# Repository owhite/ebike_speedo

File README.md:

# EBIKE SPEEDOMETER FEATURES
* Completely uninteresting 14 segment LED displays
* Serial data --> board --> BLE to smartphone
* Compatible with [MESC controller](https://github.com/davidmolony/MESC_Firmware)

## Operation
Device connects to an ESC (e.g. the [MP2](https://github.com/badgineer/CCC_ESC) with a [F405 pill](https://github.com/davidmolony/F405_pill)) and receives json data via a serial output. Typcial data stream could include:
```
{"amps": 10, "volts": 20, "rpm": 200, "temp": 90}
```
But you can configure the F405 to send other values, but the speedometer is expecting the above tags and ignores others. The speedometer uses these values as ints that will be displayed on the 14 segment LED. RPM will be converted to MPH prior to display. 

Regardless of the values or data structure received, the entired data stream is passed on to a bluetooth device which can be captured on your smartphone using an app like [Serial Bluetooth Terminal](https://play.google.com/store/apps/details?id=de.kai_morich.serial_bluetooth_terminal). 

## Programming
* Use the [STM32CubeIDE](https://www.st.com/en/development-tools/stm32cubeide.html) to progam the microcontroller on the ESC
* Use [platformio](https://platformio.org/) for the ESP32. 

## ESP32 quirks
There are conflicts between bootstrapping capability and usage of some pins. If you notice your board wont program unless you keep the button depressed, it might be due to this conflict.

This reqiures that you burn the flash voltage selection eFuses change the internal regulator’s output voltage to 3.3 V. This was fixed with using a tool from [espressif](https://docs.espressif.com/projects/esptool/en/latest/esp32s3/espefuse/index.html): 

```
$ espefuse.py set_flash_voltage 3.3V --port /dev/cu.usbserial-01562A86
```
be sure to use the appropriate port name. 

## Speedometer operation
* Assemble PCB
* Set the following parameters in ESP32 code:
```
#define POLEPAIRS    5
#define CIRCUMFERENCE 78.5 // circumference in cm of wheel
#define MAXTEMP 65 
// for the range when it provides a percentage
#define MINVOLTAGE 86.4    // lower bound of voltage
#define MAXVOLTAGE 104.0   // 24s lipos fully charge

```
* Upload code to ESP32 using platformio
* Press top button to change LED display
* Display shows: "M", "A", "V" "T" for MPH, amps, battery voltage, and temperature
* Find "ESP32 Speedometer" on your smartphone
* Gather data using an app like [Serial Bluetooth Terminal](https://play.google.com/store/apps/details?id=de.kai_morich.serial_bluetooth_terminal)
* Note on the json data there's a mS value, press lower button to reset to zero

## BOM
* Adafruit Quad Alphanumeric Display w/ backpack
* Adafruit HUZZAH32 – ESP32 Feather Board
* PCB (gerbers are [here](V1.1/gerbers))
* Two 10k 0805 resistors
* [TS14-1212-70-BK-160-SCR-D](https://www.cuidevices.com/product/resource/ts14.pdf) tactile switches
* 0.1 inch spacing header boards
* This [housing](3D_model/speedo_housing.stl) might be useful

Let's play: how tall is your stack of boards!?

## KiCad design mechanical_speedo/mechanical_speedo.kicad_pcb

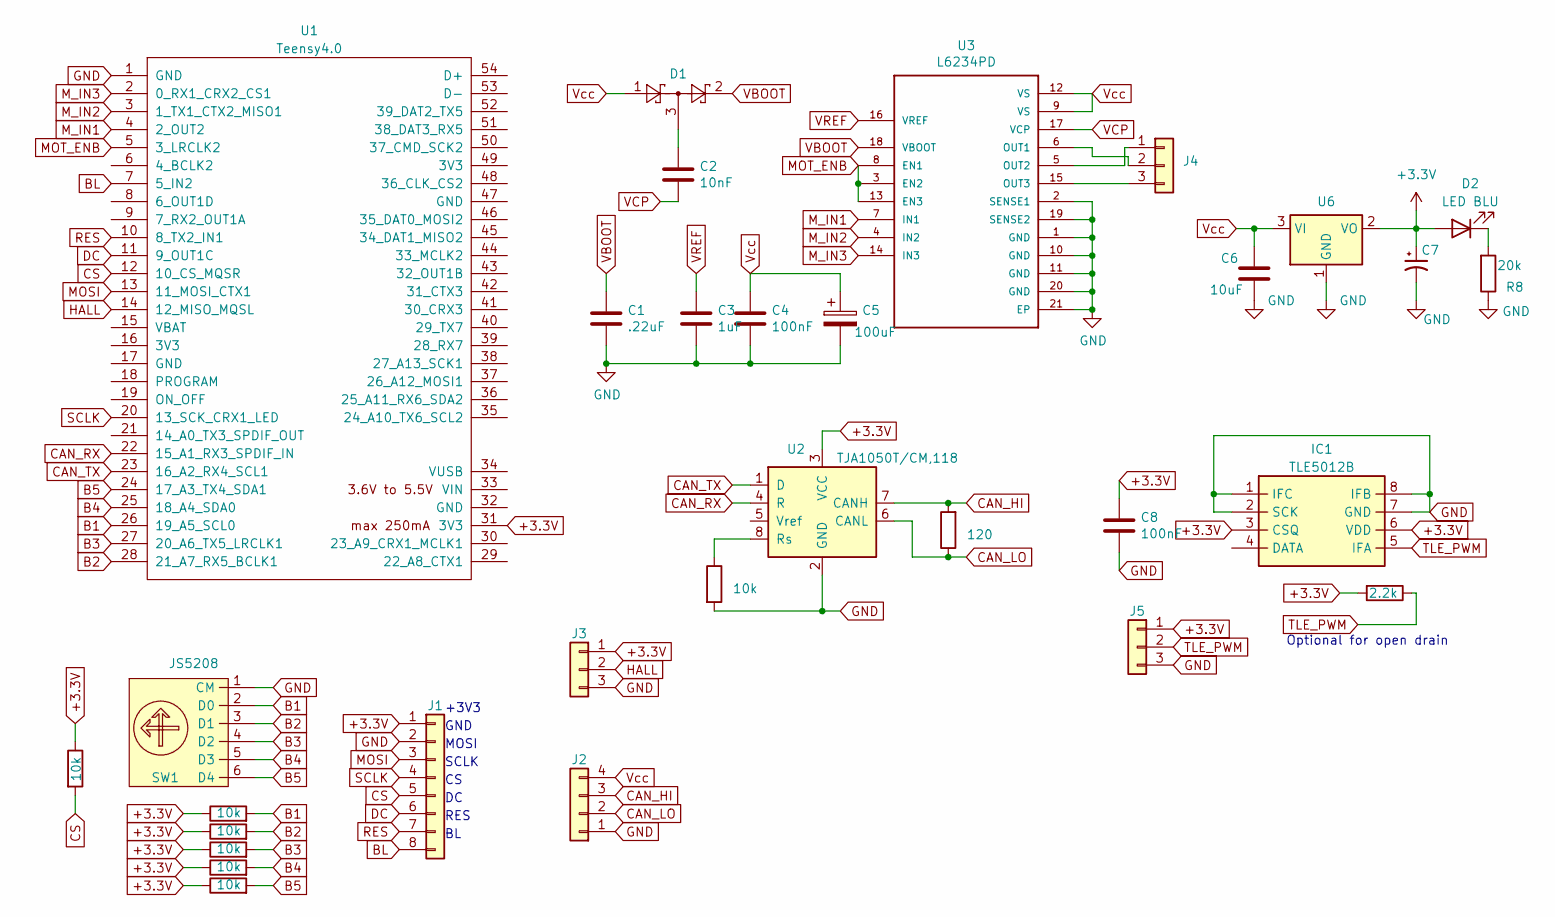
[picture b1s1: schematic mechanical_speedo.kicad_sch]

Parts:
C1: .22uF; C_0805_2012Metric; LCSC C5378
C2: 10nF; C_0603_1608Metric; LCSC C57112
C3: 1uF; C_0805_2012Metric; LCSC C28323
C4, C8: 100nF; C_0603_1608Metric; LCSC C14663
C5: 100uF; CP_EIA-3528-21_Kemet-B; LCSC C16133
C6: 10uF; C_0805_2012Metric; LCSC C15850
C7: C_Polarized_Small_US; CP_EIA-3216-18_Kemet-A; LCSC C7171
D1: BAT54S; SOT-23; LCSC C19726
D2: LED BLU; LED_0603_1608Metric; LCSC C72041
IC1: TLE5012B; SOIC127P600X175-8N; Mouser Part Number 726-TLE5012BE5000X
J1: Conn_01x08; 8_hole
J2: Conn_01x04; my_4_tab_edge
J3, J4, J5: Conn_01x03; PinHeader_1x03_P2.54mm_Vertical
R1, R2, R3, R4, R5, R6, R9: 10k; R_0805_2012Metric; LCSC C25804
R7: 120; R_0805_2012Metric; LCSC C17437
R8: 20k; R_0603_1608Metric; LCSC C4184
R11: 2.2k; R_0603_1608Metric; LCSC C4184
SW1: JS5208; SW_JS5208; LCSC C3029619
U1: Teensy4.0; Teensy32
U2: TJA1050T/CM,118; SOIC-8_3.9x4.9mm_P1.27mm; LCSC C6952
U3: L6234PD
U6: LD1117S18TR_SOT223; SOT-223-3_TabPin2; LCSC C2984862

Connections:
+3.3V: C7.1, C8.1, D2.2 (A), IC1.3 (CSQ), IC1.6 (VDD), J1.1, J3.1, J5.1, R1.1, R2.1, R4.1, R5.1, R6.1, R9.1, R11.2, U1.31 (3V3), U2.3 (VCC), U6.2 (VO)
B1: R6.2, SW1.2 (D0), U1.26 (19_A5_SCL0)
B2: R5.2, SW1.3 (D1), U1.28 (21_A7_RX5_BCLK1)
B3: R4.2, SW1.4 (D2), U1.27 (20_A6_TX5_LRCLK1)
B4: R2.2, SW1.5 (D3), U1.25 (18_A4_SDA0)
B5: R1.2, SW1.6 (D4), U1.24 (17_A3_TX4_SDA1)
BL: J1.8, U1.7 (5_IN2)
CAN_HI: J2.3, R7.2, U2.7 (CANH)
CAN_LO: J2.2, R7.1, U2.6 (CANL)
CAN_RX: U1.22 (15_A1_RX3_SPDIF_IN), U2.4 (R)
CAN_TX: U1.23 (16_A2_RX4_SCL1), U2.1 (D)
CS: J1.5, R9.2, U1.12 (10_CS_MQSR)
DC: J1.6, U1.11 (9_OUT1C)
GND: C1.2, C3.2, C4.2, C5.2, C6.2, C7.2, C8.2, IC1.1 (IFC), IC1.2 (SCK), IC1.7 (GND), IC1.8 (IFB), J1.2, J2.1, J3.3, J5.3, R3.2, R8.1, SW1.1 (CM), U1.1 (GND), U2.2 (GND), U3.1 (GND), U3.2 (SENSE1), U3.10 (GND), U3.11 (GND), U3.19 (SENSE2), U3.20 (GND), U3.21 (EP), U6.1 (GND)
HALL: J3.2, U1.14 (12_MISO_MQSL)
MOSI: J1.3, U1.13 (11_MOSI_CTX1)
MOT_ENB: U1.5 (3_LRCLK2), U3.3 (EN2), U3.8 (EN1), U3.13 (EN3)
M_IN1: U1.4 (2_OUT2), U3.7 (IN1)
M_IN2: U1.3 (1_TX1_CTX2_MISO1), U3.4 (IN2)
M_IN3: U1.2 (0_RX1_CRX2_CS1), U3.14 (IN3)
unnamed: C2.1, D1.3
unnamed: D2.1 (K), R8.2
unnamed: J4.1, U3.5 (OUT2)
unnamed: J4.2, U3.6 (OUT1)
unnamed: J4.3, U3.15 (OUT3)
unnamed: R3.1, U2.8 (Rs)
RES: J1.7, U1.10 (8_TX2_IN1)
SCLK: J1.4, U1.20 (13_SCK_CRX1_LED)
TLE_PWM: IC1.5 (IFA), J5.2, R11.1
VBOOT: C1.1, D1.2, U3.18 (VBOOT)
VCP: C2.2, U3.17 (VCP)
VREF: C3.1, U3.16 (VREF)
Vcc: C4.1, C5.1, C6.1, D1.1, J2.4, U3.9 (VS), U3.12 (VS), U6.3 (VI)

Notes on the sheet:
MOSI
Optional for open drain
RES
GND
+3V3
SCLK

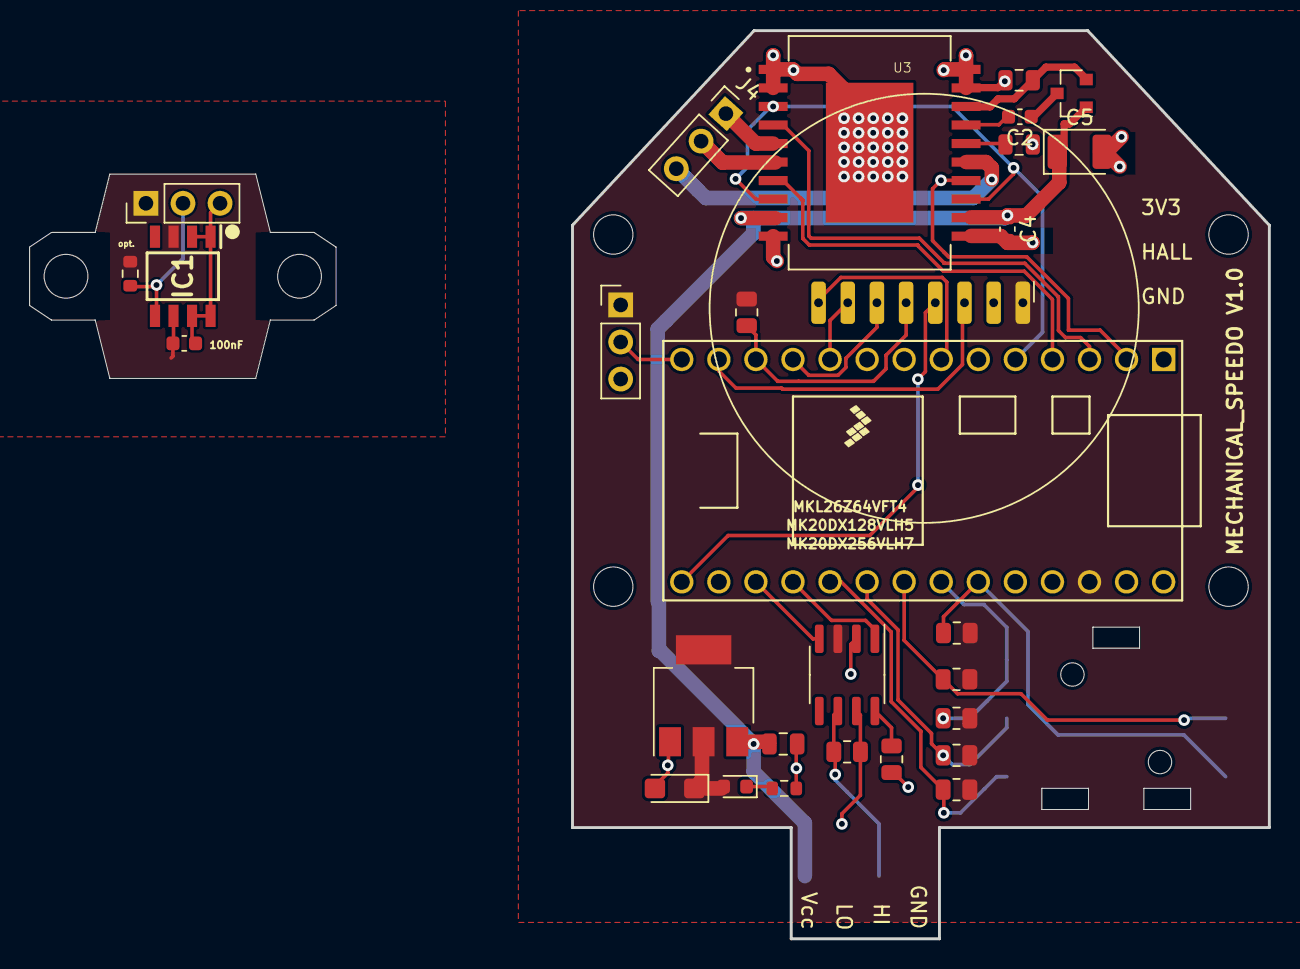
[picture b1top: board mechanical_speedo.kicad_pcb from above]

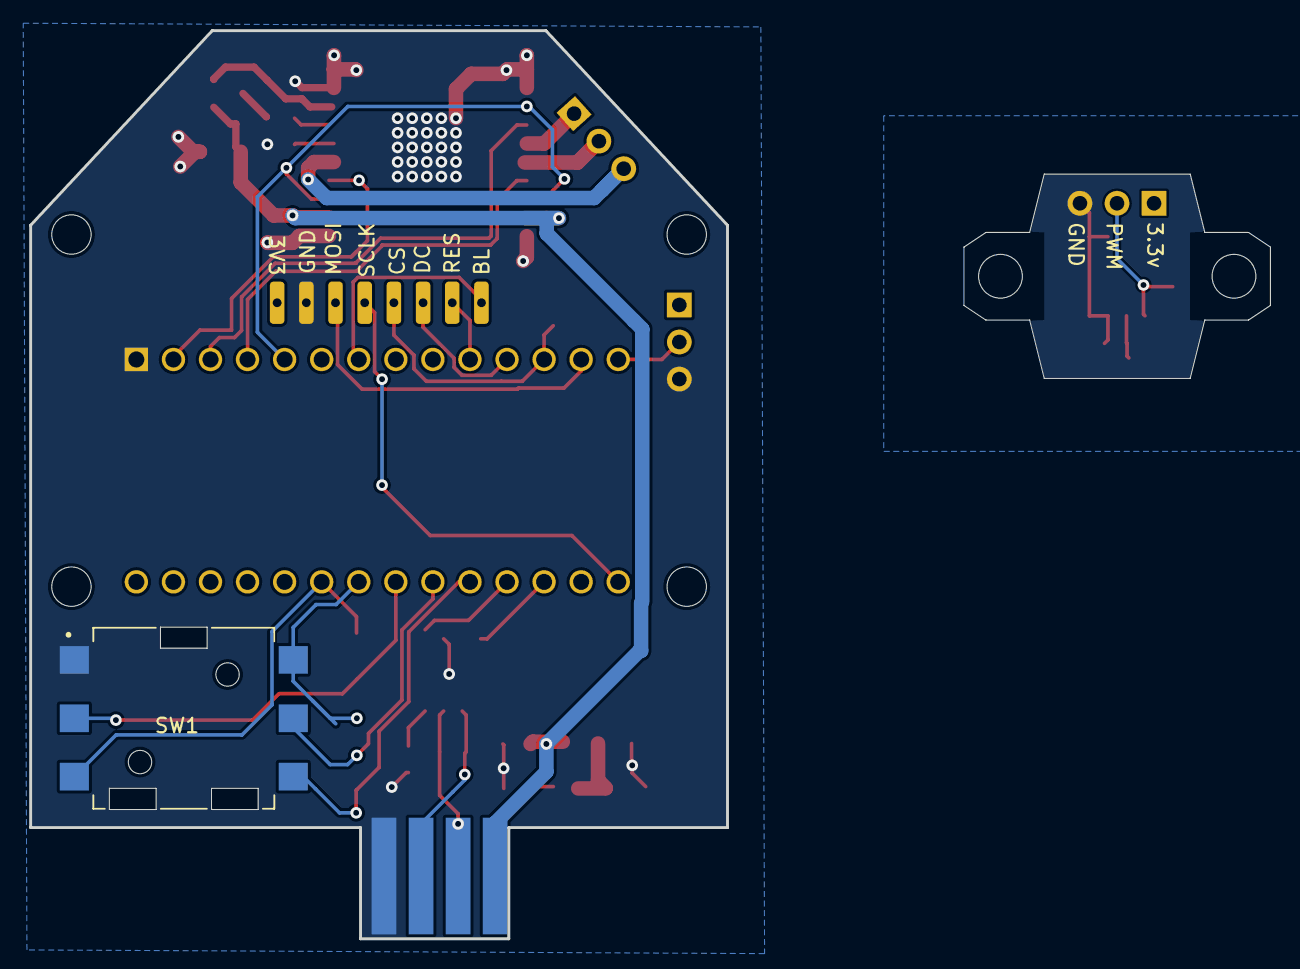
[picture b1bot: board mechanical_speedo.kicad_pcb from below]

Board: 2 copper layers, 84.9 x 62.2 mm, 31 parts (2 on the bottom side), 33 nets.

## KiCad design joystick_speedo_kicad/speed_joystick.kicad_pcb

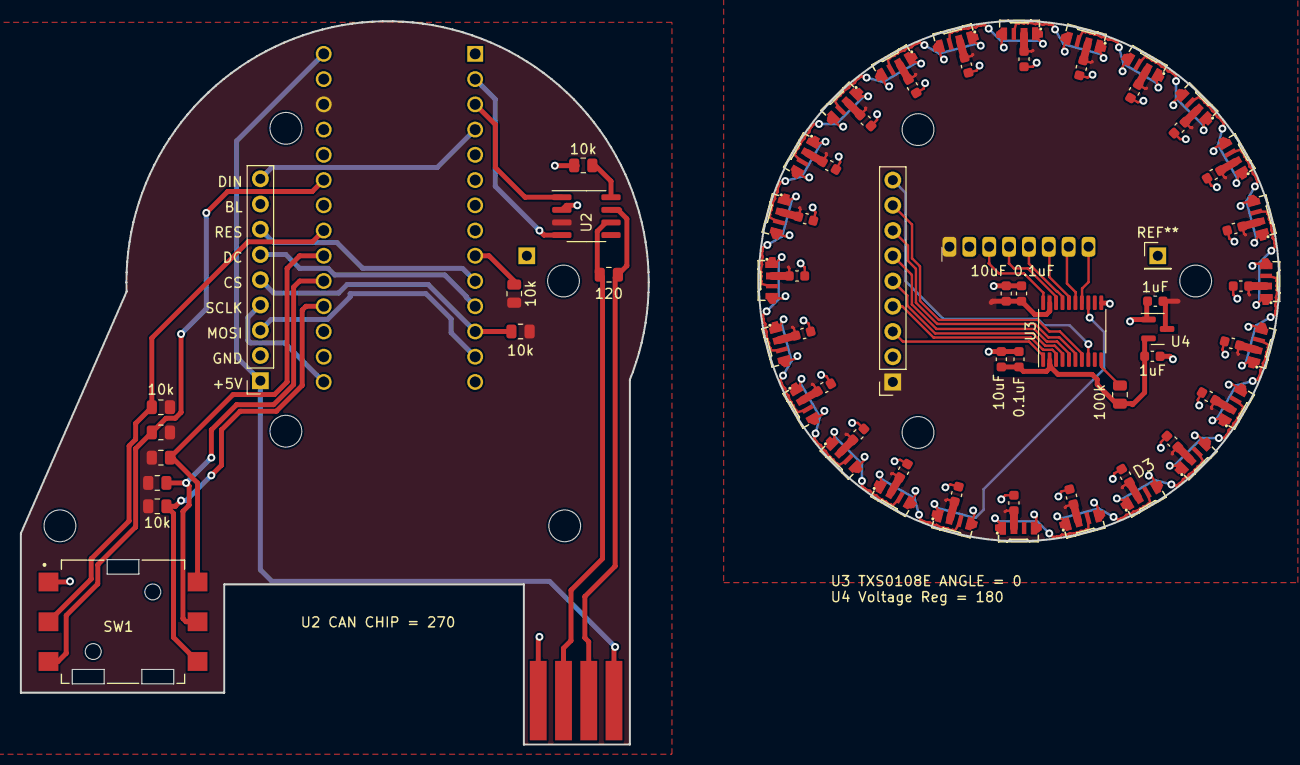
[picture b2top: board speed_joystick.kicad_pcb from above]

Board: 2 copper layers, 126.6 x 72.8 mm, 73 parts (1 on the bottom side), 62 nets.

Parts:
C1, C2, C3, C4, C5, C6, C7, C8, C9, C10, C11, C12, C13, C14, C15, C16, C17, C18, C19, C20, C21, C22, C23, C24, C25, C26: 0.1uF; C_0603_1608Metric
C27, C28: 1uF; C_0603_1608Metric
C29, C30: 10uF; C_0603_1608Metric
D1, D2, D3, D4, D5, D6, D7, D8, D9, D10, D11, D12, D13, D14, D15, D16, D17, D18, D19, D20, D21, D22, D23, D24: SK6812; LED-SMD_4P-L4.0-W1.6-L
J1: Conn_01x08; 8_hole
J2: Conn_01x04; my_4_tab_edge
J3, J4: Conn_01x09; PinSocket_1x09_P2.54mm_Vertical
R1, R2, R3, R4, R5, R6, R9, R10: 10k; R_0805_2012Metric
R7: 120; R_0805_2012Metric
R8: 100k; R_0805_2012Metric
SW1: JS5208; SW_JS5208
U1: Teensy3.2; Teensy32
U2: TJA1050T/CM,118; SOIC-8_3.9x4.9mm_P1.27mm
U3: TXS0108E; TSSOP-20_4.4x6.5mm_P0.65mm
U4: XC6206PxxxMR; SOT-23

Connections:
+3.3V: R1.1, R2.1, R4.1, R5.1, R6.1, R9.1, R10.1, U1.31 (3.3V), U2.3 (VCC)
+5V: J2.4, J4.1, U1.33 (Vin)
B1: R6.2, SW1.2 (D0), U1.26 (19_A5_SCL0_Touch)
B2: R5.2, SW1.3 (D1), U1.28 (21_A7_RX1_CS_PWM)
B3: R4.2, SW1.4 (D2), U1.25 (18_A4_SDA0_Touch)
B4: R2.2, SW1.5 (D3), U1.24 (17_A3_SDA0_Touch)
B5: R1.2, SW1.6 (D4), U1.23 (16_A2_SCL0_Touch)
BL: J4.8, U1.7 (5_TX1_PWM)
CAN_HI: J2.3, R7.2, U2.7 (CANH)
CAN_LO: J2.2, R7.1, U2.6 (CANL)
CAN_RX: U1.2 (0_RX1_Touch), U2.4 (R)
CAN_TX: U1.3 (1_TX1_Touch), U2.1 (D)
CS1: J4.5, R9.2, U1.12 (10_TX2_CS_PWM)
CS2: R10.2, U1.9 (7_RX3_DOUT)
DC: J4.6, U1.11 (9_RX2_CS_PWM)
DIN: J4.9, U1.4 (2)
DIN_SIG: D24.1 (DIN), U3.13 (B7)
GND: J2.1, J4.2, R3.2, SW1.1 (CM), U1.1 (GND), U2.2 (GND)
MOSI: J4.3, U1.13 (11_DOUT)
unnamed: D1.1 (DIN), D2.3 (DOUT)
unnamed: D2.1 (DIN), D3.3 (DOUT)
unnamed: D3.1 (DIN), D4.3 (DOUT)
unnamed: D4.1 (DIN), D5.3 (DOUT)
unnamed: D5.1 (DIN), D6.3 (DOUT)
unnamed: D6.1 (DIN), D7.3 (DOUT)
unnamed: D7.1 (DIN), D8.3 (DOUT)
unnamed: D8.1 (DIN), D9.3 (DOUT)
unnamed: D10.1 (DIN), D11.3 (DOUT)
unnamed: D9.1 (DIN), D10.3 (DOUT)
unnamed: D11.1 (DIN), D12.3 (DOUT)
unnamed: D12.1 (DIN), D13.3 (DOUT)
unnamed: D13.1 (DIN), D14.3 (DOUT)
unnamed: D14.1 (DIN), D15.3 (DOUT)
unnamed: D15.1 (DIN), D16.3 (DOUT)
unnamed: D16.1 (DIN), D17.3 (DOUT)
unnamed: D17.1 (DIN), D18.3 (DOUT)
unnamed: D18.1 (DIN), D19.3 (DOUT)
unnamed: D19.1 (DIN), D20.3 (DOUT)
unnamed: D20.1 (DIN), D21.3 (DOUT)
unnamed: D21.1 (DIN), D22.3 (DOUT)
unnamed: D22.1 (DIN), D23.3 (DOUT)
unnamed: D23.1 (DIN), D24.3 (DOUT)
unnamed: J1.3, U3.20 (B1)
unnamed: J1.4, U3.18 (B2)
unnamed: J1.5, U3.17 (B3)
unnamed: J1.6, U3.16 (B4)
unnamed: J1.7, U3.15 (B5)
unnamed: J1.8, U3.14 (B6)
unnamed: R3.1, U2.8 (Rs)
unnamed: R8.2, U3.10 (OE)
RES: J4.7, U1.10 (8_TX3_DIN)
R_+3.3V: C25.1, C27.1, C30.1, R8.1, U3.2 (VCCA), U4.2 (VO)
R_+5V: C1.1, C2.1, C3.1, C4.1, C5.1, C6.1, C7.1, C8.1, C9.1, C10.1, C11.1, C12.1, C13.1, C14.1, C15.1, C16.1, C17.1, C18.1, C19.1, C20.1, C21.1, C22.1, C23.1, C24.1, C26.1, C28.1, C29.1, D1.2 (VDD), D2.2 (VDD), D3.2 (VDD), D4.2 (VDD), D5.2 (VDD), D6.2 (VDD), D7.2 (VDD), D8.2 (VDD), D9.2 (VDD), D10.2 (VDD), D11.2 (VDD), D12.2 (VDD), D13.2 (VDD), D14.2 (VDD), D15.2 (VDD), D16.2 (VDD), D17.2 (VDD), D18.2 (VDD), D19.2 (VDD), D20.2 (VDD), D21.2 (VDD), D22.2 (VDD), D23.2 (VDD), D24.2 (VDD), J1.1, J3.1, U3.19 (VCCB), U4.3 (VI)
R_BL: J3.8, U3.7 (A6)
R_CS: J3.5, U3.4 (A3)
R_DC: J3.6, U3.5 (A4)
R_DIN: J3.9, U3.8 (A7)
R_GND: C1.2, C2.2, C3.2, C4.2, C5.2, C6.2, C7.2, C8.2, C9.2, C10.2, C11.2, C12.2, C13.2, C14.2, C15.2, C16.2, C17.2, C18.2, C19.2, C20.2, C21.2, C22.2, C23.2, C24.2, C25.2, C26.2, C27.2, C28.2, C29.2, C30.2, D1.4 (VSS), D2.4 (VSS), D3.4 (VSS), D4.4 (VSS), D5.4 (VSS), D6.4 (VSS), D7.4 (VSS), D8.4 (VSS), D9.4 (VSS), D10.4 (VSS), D11.4 (VSS), D12.4 (VSS), D13.4 (VSS), D14.4 (VSS), D15.4 (VSS), D16.4 (VSS), D17.4 (VSS), D18.4 (VSS), D19.4 (VSS), D20.4 (VSS), D21.4 (VSS), D22.4 (VSS), D23.4 (VSS), D24.4 (VSS), J1.2, J3.2, U3.11 (GND), U4.1 (GND)
R_MOSI: J3.3, U3.1 (A1)
R_RES: J3.7, U3.6 (A5)
R_SCLK: J3.4, U3.3 (A2)
SCLK: J4.4, U1.20 (13_LED_SCK)

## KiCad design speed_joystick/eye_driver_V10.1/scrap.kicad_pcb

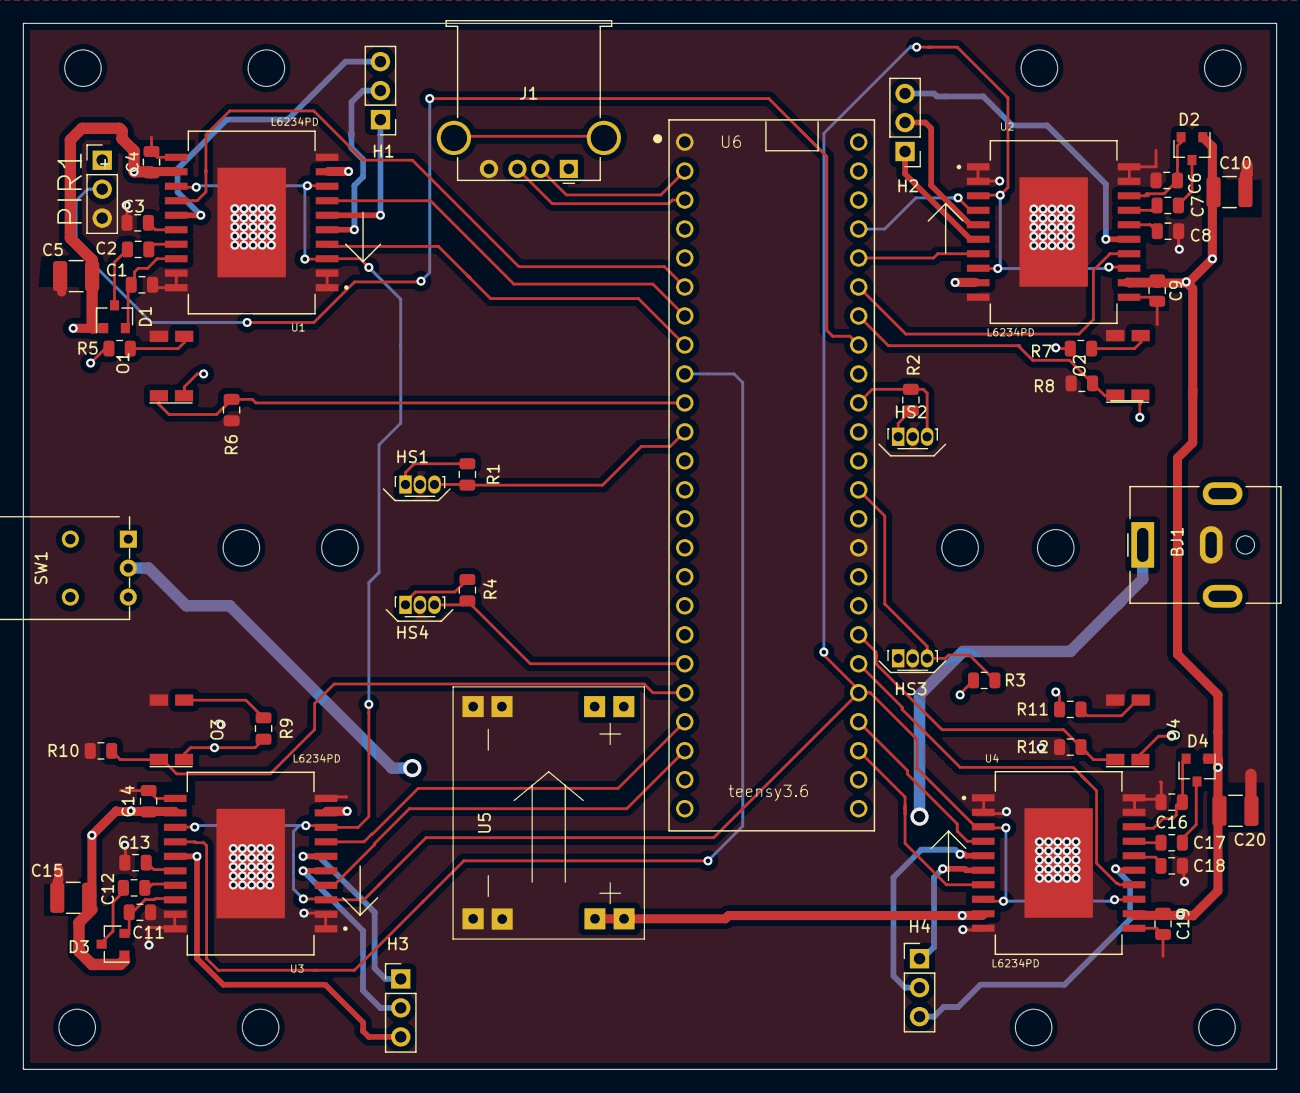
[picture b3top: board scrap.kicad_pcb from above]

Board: 4 copper layers, 109.8 x 91.7 mm, 58 parts (0 on the bottom side), 60 nets.

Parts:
BJ1: Barrel_Jack; BarrelJack_CUI_PJ-063AH_Horizontal
C1, C6, C11, C16: .22uF; C_0805_2012Metric
C2, C7, C12, C17: 10nF; C_0805_2012Metric
C3, C8, C13, C18: 1uF; C_0805_2012Metric
C4, C9, C14, C19: 100nF; C_0805_2012Metric
C5, C10, C15, C20: 100uF; C_1210_3225Metric
D1, D2, D3, D4: BAT54S; SOT-23
H1, H2, H3, H4: Conn_01x03; PinHeader_1x03_P2.54mm_Vertical
HS1, HS2, HS3, HS4: hall_effect_three_wire; Diodes_SIP-3_4.1x1.5mm_P1.27mm
J1: USB_A; USB_A_Stewart_SS-52100-001_Horizontal
O1, O2, O3, O4: my_optical_switch; my_slotted_switch
PIR1: Conn_01x03; PinHeader_1x03_P2.54mm_Vertical
R1, R2, R3, R4: 50k; R_0805_2012Metric
R5, R7, R9, R11: 110; R_0805_2012Metric
R6, R8, R10, R12: 10k; R_0805_2012Metric
SW1: SW_SPDT; SW_NKK_BB15AH
U1, U2, U3, U4: L6234PD; SOIC127P1420X360-21N
U5: my_buck_boost
U6: teensy3.6; MODULE_DEV-14058

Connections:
+3.3v: HS1.1, HS2.1, HS3.1, HS4.1, J1.1, O1.4, O2.4, O3.4, O4.4, PIR1.1, R1.1, R2.1, R3.1, R4.1, R5.1, R7.1, R9.1, R11.1, U5.7, U5.8, U6.3.3V
GND: BJ1.2, C1.2, C3.2, C4.2, C5.2, C6.2, C8.2, C9.2, C10.2, C11.2, C13.2, C14.2, C15.2, C16.2, C18.2, C19.2, C20.2, HS1.2, HS2.2, HS3.2, HS4.2, J1.4, O1.2, O2.2, O3.2, O4.2, PIR1.3, R6.2, R8.2, R10.2, R12.2, U1.1, U1.2, U1.10, U1.11, U1.19, U1.20, U1.21, U2.1, U2.2, U2.10, U2.11, U2.19, U2.20, U2.21, U3.1, U3.2, U3.10, U3.11, U3.19, U3.20, U3.21, U4.1, U4.2, U4.10, U4.11, U4.19, U4.20, U4.21, U5.1, U5.2, U5.5, U5.6, U6.GND1, U6.GND2
HS1: HS1.3, R1.2, U6.9
HS2: HS2.3, R2.2, U6.17
HS3: HS3.3, R3.2, U6.14
HS4: HS4.3, R4.2, U6.27
M1_IN1: U1.7, U6.5
M1_IN2: U1.4, U6.6
M1_IN3: U1.14, U6.4
M2_IN1: U2.7, U6.22
M2_IN2: U2.4, U6.23
M2_IN3: U2.14, U6.21
M3_IN1: U3.7, U6.29
M3_IN2: U3.4, U6.30
M3_IN3: U3.14, U6.7
M4_IN1: U4.7, U6.35
M4_IN2: U4.4, U6.36
M4_IN3: U4.14, U6.38
M_EN: U1.3, U1.8, U1.13, U2.3, U2.8, U2.13, U3.3, U3.8, U3.13, U4.3, U4.8, U4.13, U6.37
unnamed: BJ1.1, SW1.2
unnamed: C2.1, D1.3
unnamed: C7.1, D2.3
unnamed: C12.1, D3.3
unnamed: C17.1, D4.3
unnamed: O1.1, R5.2
unnamed: O2.1, R7.2
unnamed: O3.1, R9.2
unnamed: O4.1, R11.2
OS1: O1.3, R6.1, U6.8
OS2: O2.3, R8.1, U6.20
OS3: O3.3, R10.1, U6.28
OS4: O4.3, R12.1, U6.39
PIR: PIR1.2, U6.19
RX: J1.2, U6.0
TX: J1.3, U6.1
U1: H1.1, U1.6
U2: H2.1, U2.6
U3: H3.1, U3.6
U4: H4.1, U4.6
V1: H1.2, U1.5
V2: H2.2, U2.5
V3: H3.2, U3.5
V4: H4.2, U4.5
VBOOT1: C1.1, D1.2, U1.18
VBOOT2: C6.1, D2.2, U2.18
VBOOT3: C11.1, D3.2, U3.18
VBOOT4: C16.1, D4.2, U4.18
VCP1: C2.2, U1.17
VCP2: C7.2, U2.17
VCP3: C12.2, U3.17
VCP4: C17.2, U4.17
VREF1: C3.1, U1.16
VREF2: C8.1, U2.16
VREF3: C13.1, U3.16
VREF4: C18.1, U4.16
Vcc: C4.1, C5.1, C9.1, C10.1, C14.1, C15.1, C19.1, C20.1, D1.1, D2.1, D3.1, D4.1, SW1.1, U1.9, U1.12, U2.9, U2.12, U3.9, U3.12, U4.9, U4.12, U5.3, U5.4
W1: H1.3, U1.15
W2: H2.3, U2.15
W3: H3.3, U3.15
W4: H4.3, U4.15

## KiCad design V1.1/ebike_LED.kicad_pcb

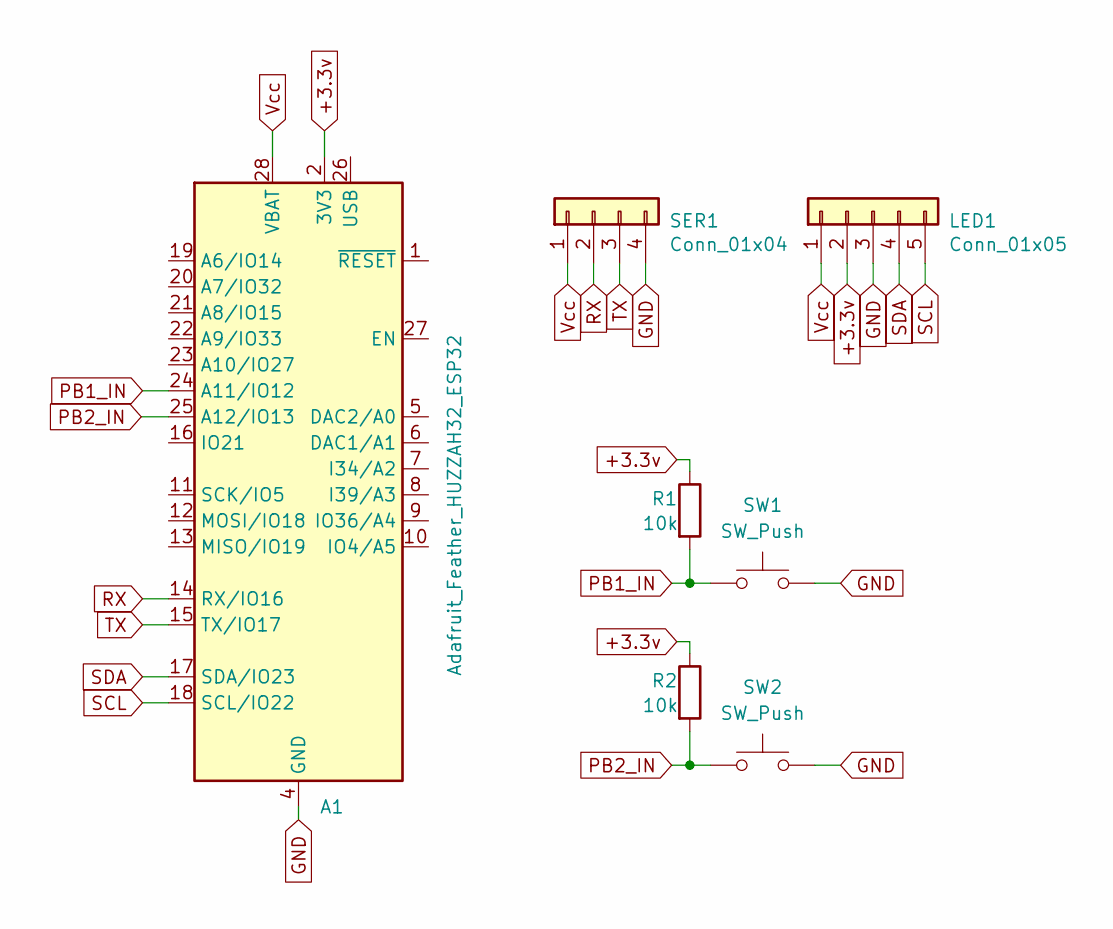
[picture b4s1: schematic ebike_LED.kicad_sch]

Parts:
A1: Adafruit_Feather_HUZZAH32_ESP32; Adafruit_Feather
LED1: Conn_01x05; PinHeader_1x05_P2.54mm_Vertical
R1, R2: 10k; R_0805_2012Metric
SER1: Conn_01x04; PinHeader_1x04_P2.54mm_Vertical
SW1, SW2: SW_Push; SW_PUSH-12mm

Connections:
+3.3v: A1.2 (3V3), LED1.2, R1.1, R2.1
GND: A1.4 (GND), LED1.3, SER1.4, SW1.2, SW2.2
PB1_IN: A1.24 (A11/IO12), R1.2, SW1.1
PB2_IN: A1.25 (A12/IO13), R2.2, SW2.1
RX: A1.14 (RX/IO16), SER1.2
SCL: A1.18 (SCL/IO22), LED1.5
SDA: A1.17 (SDA/IO23), LED1.4
TX: A1.15 (TX/IO17), SER1.3
Vcc: A1.28 (VBAT), LED1.1, SER1.1

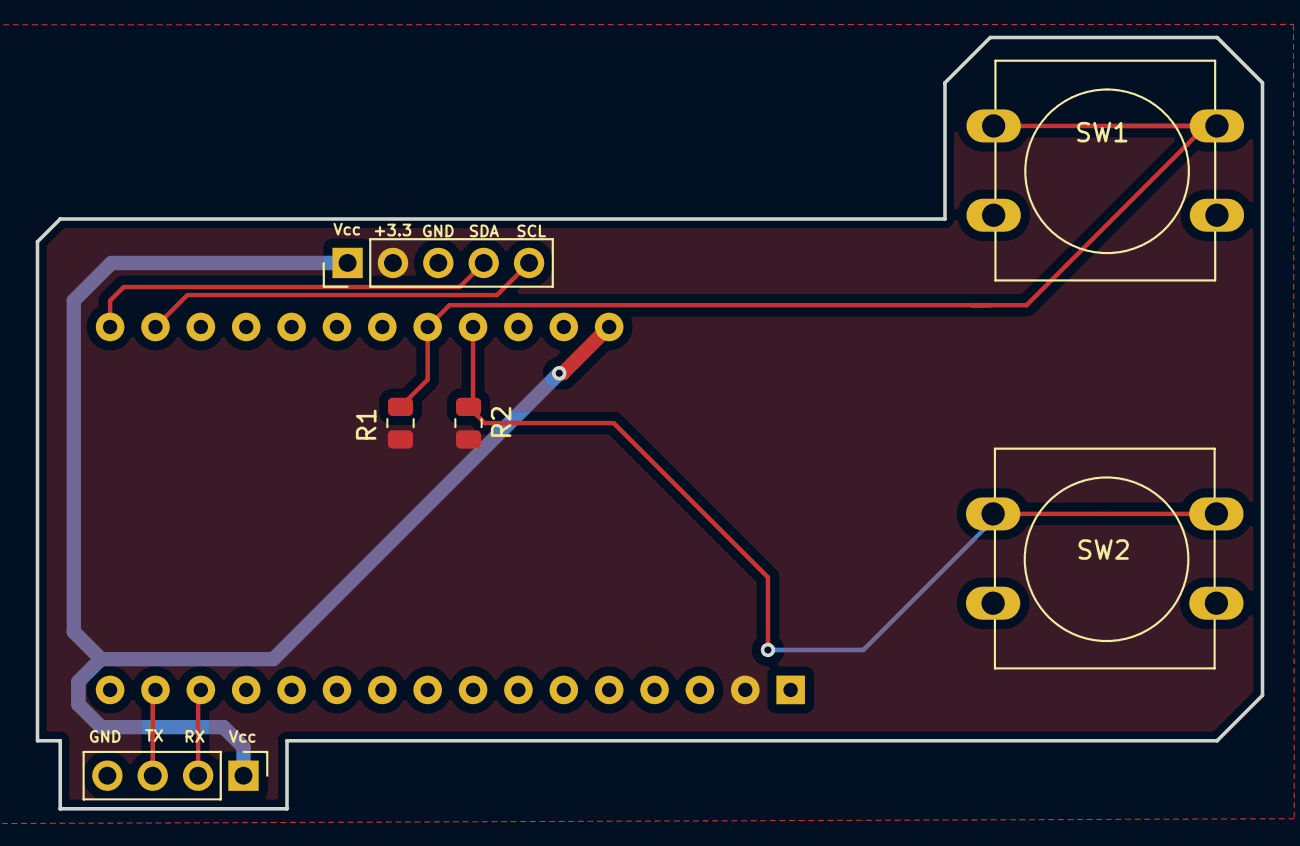
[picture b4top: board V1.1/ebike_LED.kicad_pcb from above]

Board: 2 copper layers, 68.6 x 43.2 mm, 7 parts (1 on the bottom side), 9 nets.

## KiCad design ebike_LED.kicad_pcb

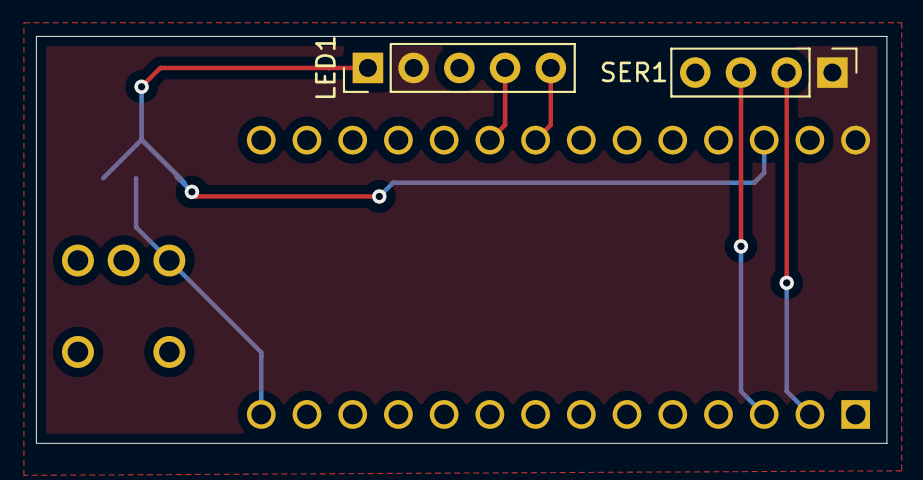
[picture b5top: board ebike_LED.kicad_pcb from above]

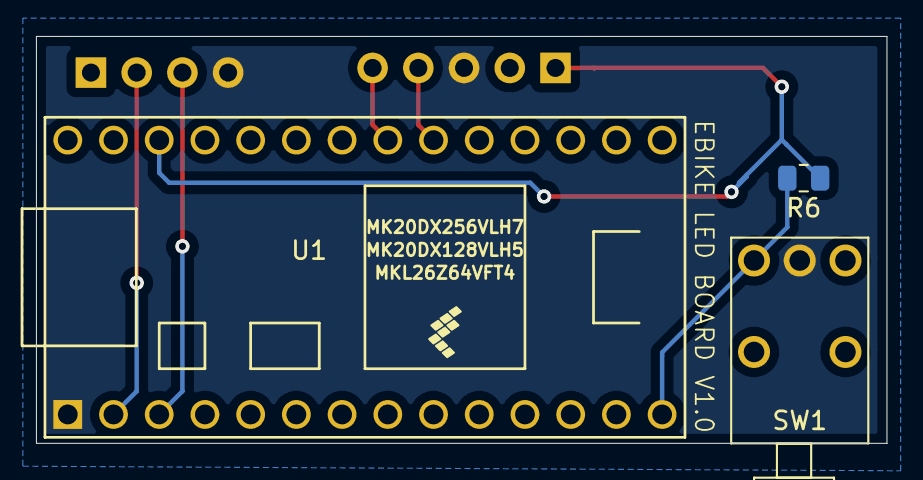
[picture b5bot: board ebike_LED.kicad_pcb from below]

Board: 2 copper layers, 47.2 x 22.6 mm, 5 parts (3 on the bottom side), 8 nets.

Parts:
LED1: Conn_01x05; PinHeader_1x05_P2.54mm_Vertical
R6: 10k; R_0805_2012Metric
SER1: Conn_01x04; PinHeader_1x04_P2.54mm_Vertical
SW1: Conn_01x02; my_pushbutton
U1: Teensy3.2; Teensy32

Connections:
+3.3v: LED1.1, R6.1, U1.31
GND: LED1.3, SER1.4, SW1.2, U1.1
PB1_IN: R6.2, SW1.1, U1.14
Rx-BESC: SER1.3, U1.3
SCL: LED1.5, U1.26
SDA: LED1.4, U1.25
Tx-BESC: SER1.2, U1.2
Vcc: LED1.2, SER1.1, U1.33

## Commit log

2022-11-28 started V1.1
2022-11-28 gerber generation
2022-12-06 added esp32 code
2022-12-06 stuff
2022-12-06 added LED code
2022-12-06 added stuff
2022-12-06 added pics
2022-12-06 file cleanup
2022-12-11 added STM32cube project
2022-12-11 arduino code work
2022-12-11 added 3d stuff
2022-12-11 edit to readme
2022-12-12 new pic
2022-12-12 edits
2022-12-12 adjusted files
2022-12-13 fixed timer reset
2023-02-21 working code
2023-03-05 works with BT
2023-04-03 added kill switch
2023-04-07 testing
2023-04-12 added the CAN SAME51
2023-04-12 added CAN
2023-04-12 changed directory name
2023-04-12 lots of CAN changes
2023-04-13 broke a bunch of timer issues
2023-04-14 added button press
2023-04-16 added more stuff
2023-04-20 minor fixes to CAN values
2023-04-21 added debug_print
2023-04-25 improved error reporting
2023-05-01 added ring_can_speedo
2023-05-01 added neopixel code
2023-05-02 added DigiFont
2023-05-02 added bitmaps
2023-05-02 added pretty font
2023-05-03 added displayNum
2023-05-04 started menu system
2023-05-04 progress on menus
2023-05-05 more menu additions
2023-05-05 menu refinement
2023-05-07 more menu work
2023-05-09 menu work
2023-05-09 layout testing
2023-05-12 combined into oled_speedo
2023-05-18 added joystick speedo
2023-05-18 pcb work
2023-05-23 work on speed_joystick pcb
2023-05-31 more round oled work
2023-06-01 more menu refinement
2023-06-02 refining functionality
2023-06-19 created V1.2
2023-06-19 finalized speed_joystick V1.2
2023-06-19 create jlcpcb order
2023-06-27 discovered some lost files
2023-06-28 important oled_round files found
2023-06-28 rearranged files -> folders
2023-06-28 writes to eeprom
2023-09-05 created mechanical_speedo
2023-09-19 playing around with motor_test
2023-09-27 added encoder board to mechanical_speedo
2026-02-10 serial input to ATSAME51_CAN
